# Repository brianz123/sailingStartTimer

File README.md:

# Sailing Start Timer

This project is a microcontroller-based horn system designed to automate race starts for sailboat regattas. It replaces manual countdowns and whistle systems with a reliable, consistent, and rugged solution tailored to race officials on the water.

## Summary

The Sailing Start Timer outputs a sequence of horn blasts that follow standard sailing race countdown rules. A single button press initiates the sequence, allowing race officials to focus on managing boats instead of watching the clock. The system is built with an Arduino and a waterproof speaker, and was designed to be both portable and weather-resistant.

## Features

- Automated horn sequence for 5-minute, 3-minute, or custom countdowns
- One-button operation for simple race start triggering
- Loud, waterproof horn for outdoor use
- Rugged and portable design suitable for mark boats or committee boats
- Custom enclosure and PCB designed for durability

## Hardware

- Arduino microcontroller
- Waterproof speaker module
- Push-button input
- Custom 3D-printed or machined enclosure
- Power system for extended outdoor operation (e.g. 12V or battery pack)

## Software

- Written in Arduino C++
- Timer-based logic to produce horn blasts at key intervals
- Debounced user input handling
- Configurable countdown intervals via code or DIP switches (if implemented)

## How It Works

1. User presses a button to trigger the countdown.
2. The microcontroller runs a timed sequence of horn blasts:
   - Long horn at 5:00
   - Warning signals at 4:00, 1:00, and 0:00 (based on racing rules)
3. Horn blasts are output through a waterproof horn module at full volume.
4. System resets automatically or after user input.

## Use Case

This device is intended for use by sailing race officials on the water. It simplifies race starts, ensures consistent timing, and reduces errors from manual systems.

## Author

**Brian Zagalsky**

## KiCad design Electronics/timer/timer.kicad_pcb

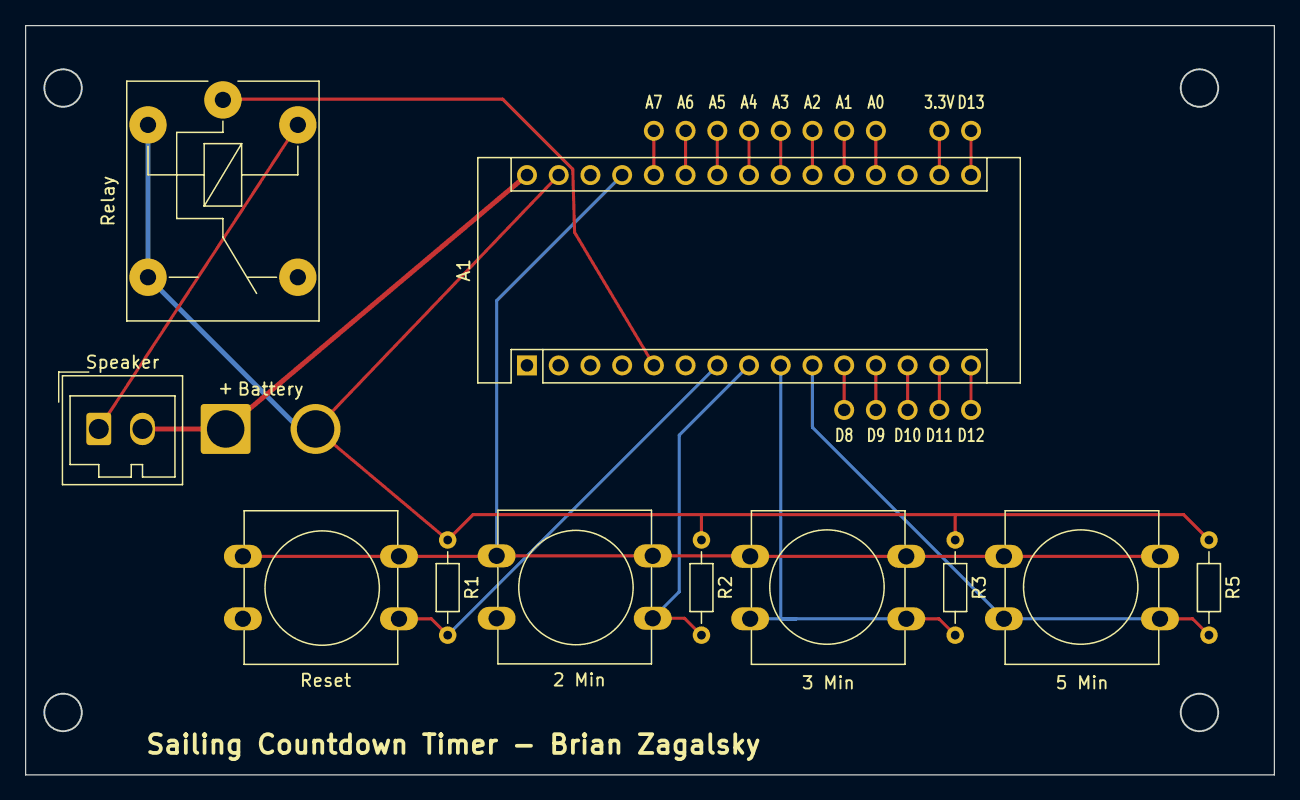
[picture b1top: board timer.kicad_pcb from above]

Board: 2 copper layers, 100.0 x 59.9 mm, 27 parts (0 on the bottom side), 9 nets.

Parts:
3.3V: MountingHole_1.2mm
A0, A1, A2, A3, A4, A5, A6, A7: MountingHole_1.2mm
A1#2: Arduino_Nano_v3.x; Arduino_Nano
Battery: Battery; SolderWire-2.5sqmm_1x02_P7.2mm_D2.4mm_OD3.6mm
D8, D9, D10, D11, D12, D13: MountingHole_1.2mm
R1, R2, R3, R5: 10k; R_Axial_DIN0204_L3.6mm_D1.6mm_P7.62mm_Horizontal
Relay: FINDER-36.11; Relay_SPDT_Finder_36.11
SW1: Reset; SW_PUSH-12mm
SW2: 2 Min; SW_PUSH-12mm
SW3: 3 Min; SW_PUSH-12mm
SW4: 5 Min; SW_PUSH-12mm
Speaker: Speaker; Wago_734-132_1x02_P3.50mm_Vertical

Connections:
unnamed: A1#2.5 (D2), Relay.11
unnamed: Relay.A2, Speaker.1
unnamed: A1#2.30 (VIN), Battery.1 (+), Speaker.2
unnamed: A1#2.7 (D4), R1.2, SW1.2
unnamed: A1#2.8 (D5), R2.2, SW2.2
unnamed: A1#2.9 (D6), R3.2, SW3.1
unnamed: A1#2.10 (D7), R5.2, SW4.1
unnamed: A1#2.27 (+5V), SW1.1, SW2.1, SW3.2, SW4.2
unnamed: A1#2.29 (GND), Battery.2 (-), R1.1, R2.1, R3.1, R5.1, Relay.14, Relay.A1

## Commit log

2024-07-31 Initial push
